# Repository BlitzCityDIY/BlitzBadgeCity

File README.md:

# BlitzBadgeCity
A blinky LMC555 timer-based badge

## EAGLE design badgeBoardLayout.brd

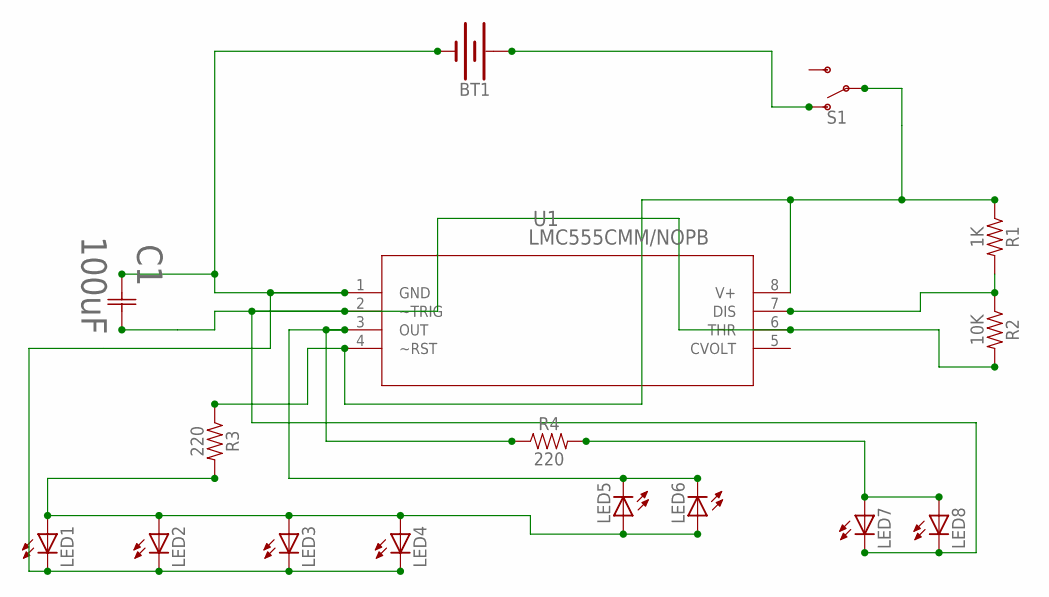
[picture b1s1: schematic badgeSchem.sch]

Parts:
BT1: BATTERY-12MM_PTH; BATTCON_12MM_PTH
C1: 100uF; CAP_2012-M
LED1, LED2, LED3, LED4, LED5, LED6, LED7, LED8: LEDSML0805; SML0805
R1: 1K; 0805
R2: 10K; 0805
R3, R4: 220; 0805
S1: SWITCH-SPDT-SMD-RIGHT-ANGLE; SWITCH_SPST_SMD_A
U1: LMC555CMM/NOPB; MUA08A

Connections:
unnamed: C1.2 (22), LED7.C, LED8.C, R2.2, U1.2 (~TRIG), U1.6 (THR)
unnamed: R1.2, R2.1, U1.7 (DIS)
unnamed: BT1.GND (-), C1.1 (11), LED1.C, LED2.C, LED3.C, LED4.C, U1.1 (GND)
unnamed: R1.1, R3.1, S1.2, U1.4 (~RST), U1.8 (V+)
unnamed: LED1.A, LED2.A, LED3.A, LED4.A, LED5.A, LED6.A, R3.2
unnamed: LED5.C, LED6.C, R4.1, U1.3 (OUT)
unnamed: LED7.A, LED8.A, R4.2
unnamed: BT1.VCC@1 (+), S1.1 (O)

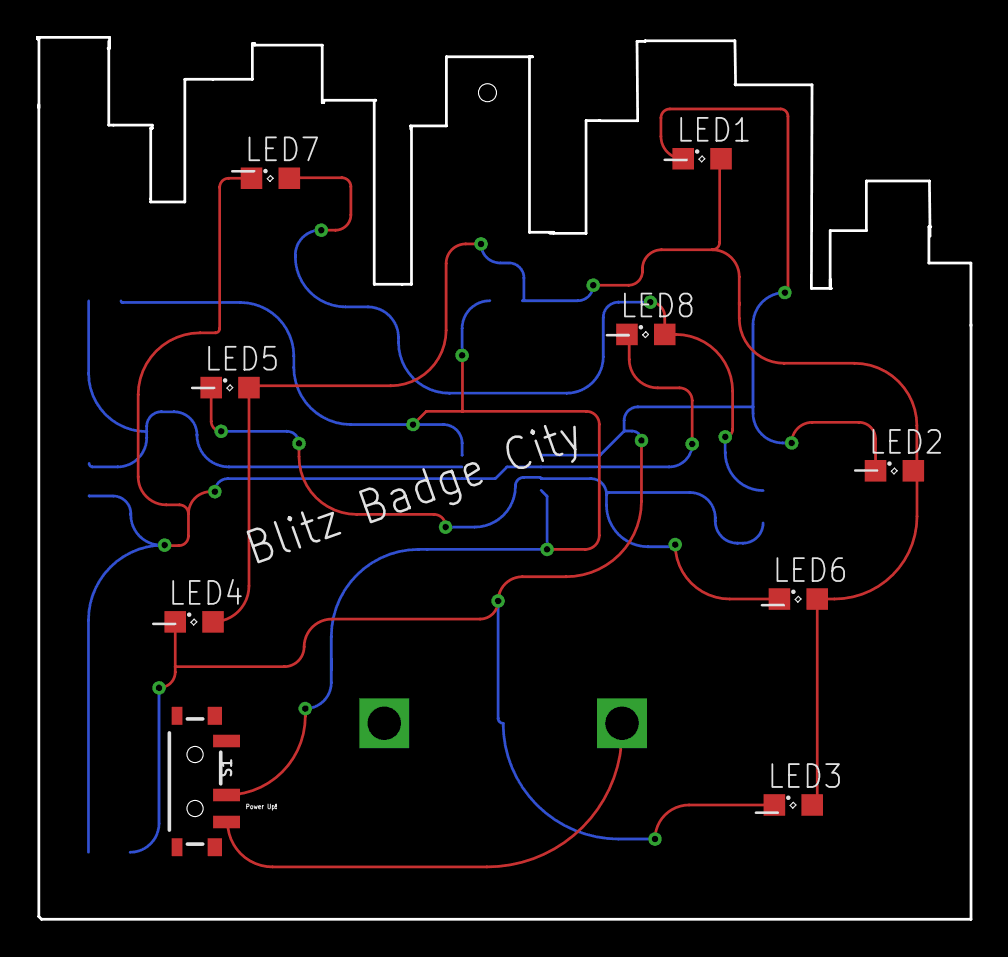
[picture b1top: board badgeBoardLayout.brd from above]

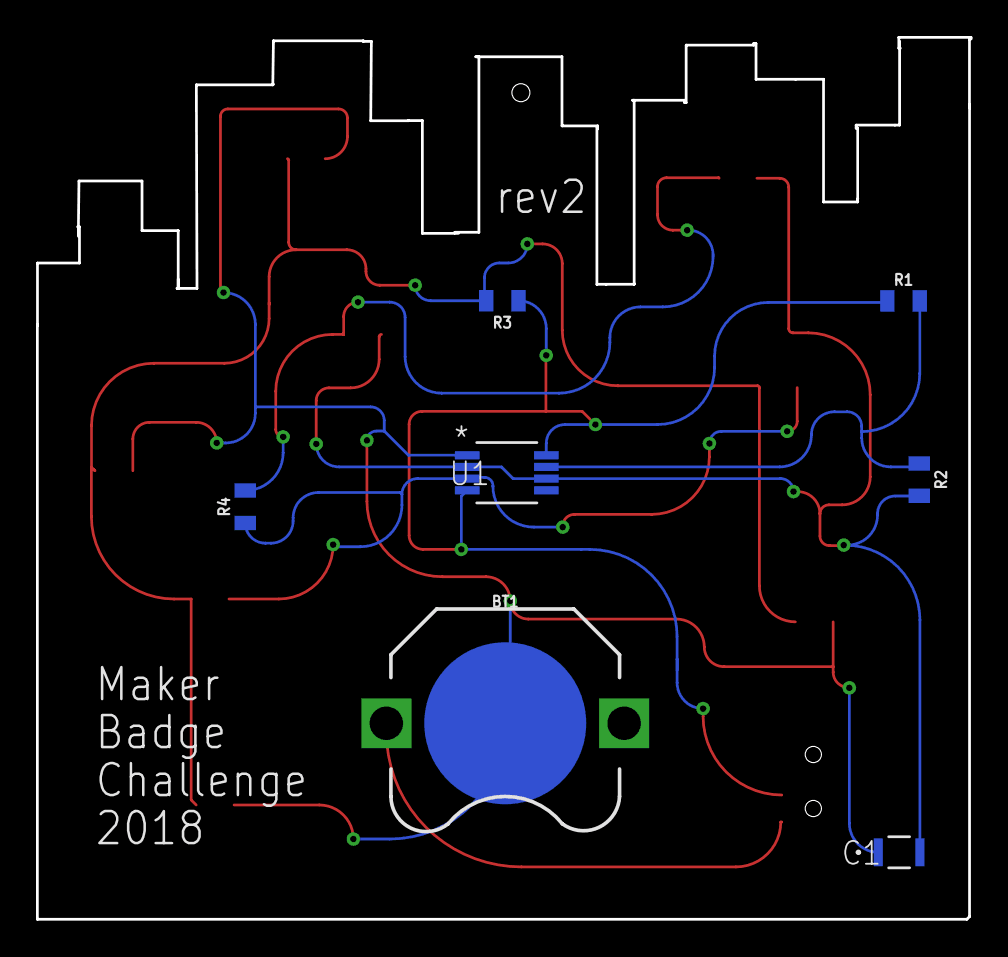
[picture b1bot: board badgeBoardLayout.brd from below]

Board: 2 copper layers, 51.9 x 49.0 mm, 16 parts (7 on the bottom side), 8 nets.

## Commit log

2018-11-30 Eagle files for the schematic, board layout & BOM

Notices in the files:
parts and their libraries:
SparkFun-Resistors: Licensing: Creative Commons ShareAlike 4.0 International - https://creativecommons.org/licenses/by-sa/4.0
